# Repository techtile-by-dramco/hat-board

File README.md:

# HAT board ✅

This PCB was developed by Guus Leenders from KU Leuven DRAMCO and should be connected to the RPI 4 on all 140 tiles.
The board is utilized in a distributed antenna or **Radioweave** infrastructure and his main function is controlling the PLL board and OLED screen. 
This HAT board has a flat cable connector to control the PLL board (see [pll-oled-hat](https://github.com/techtile-by-dramco/pll-oled-hat))

All HAT board functions listed:
* 1x Flat cable connector (PLL board connection)
* 5x Addressable RGB LEDs
* 2x User buttons
* 1x HAT output connector
* 1x OLED screen
* 1x Proximity sensor

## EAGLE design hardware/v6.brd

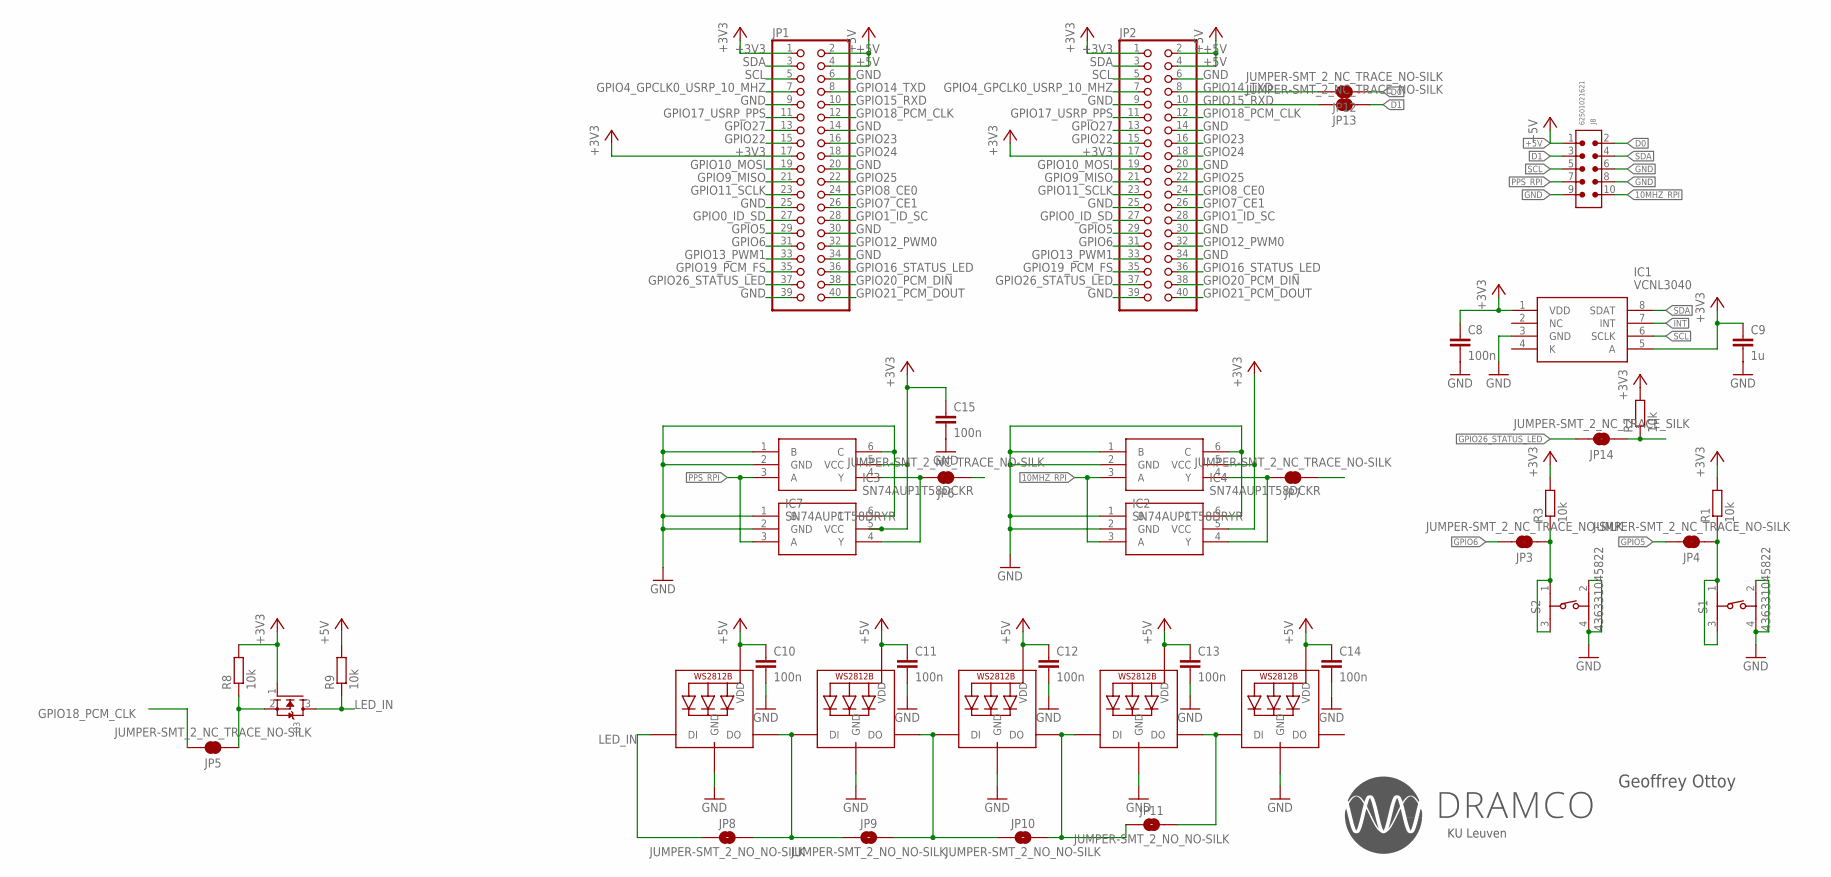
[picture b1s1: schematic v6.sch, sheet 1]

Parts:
C8, C10, C11, C12, C13, C14, C15: 100n; C0603
C9: 1u; C0603
IC1: VCNL3040; SON108P200X400X115-8N
IC2, IC7: SN74AUP1T58DRYR; SON50P100X145X60-6N
IC3, IC4: SN74AUP1T58DCKR; SOT65P210X110-6N
J8: 62501021621
JP1: PINHD-2X20; 2X20
JP2: PINHD-2X20/90; 2X20/90
JP3, JP4, JP5, JP6, JP7, JP12, JP13: JUMPER-SMT_2_NC_TRACE_NO-SILK; SMT-JUMPER_2_NC_TRACE_NO-SILK
JP8, JP9, JP10, JP11: JUMPER-SMT_2_NO_NO-SILK; SMT-JUMPER_2_NO_NO-SILK
JP14: JUMPER-SMT_2_NC_TRACE_SILK; SMT-JUMPER_2_NC_TRACE_SILK
LED1, LED2, LED3, LED4, LED5: WS2812B5050; WS2812B
Q3: MOSFET-NREFLOW; SOT23
R1, R2, R3, R8, R9: 10k; R0603
S1, S2: 436331045822; 4363X10458XX

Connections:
10MHZ_RPI: IC2.3 (A), IC4.3 (A), J8.10
+3V3: C8.1, C9.1, C15.1, IC1.1 (VDD), IC1.5 (A), IC2.5 (VCC), IC3.5 (VCC), IC4.5 (VCC), IC7.5 (VCC), JP1.1, JP1.17, JP2.1, JP2.17, Q3.1 (G), R1.2, R2.2, R3.2, R8.2; also elsewhere on the board
+5V: C10.1, C11.1, C12.1, C13.1, C14.1, J8.1, JP1.2, JP1.4, JP2.2, JP2.4, LED1.1-VDD (VDD), LED2.1-VDD (VDD), LED3.1-VDD (VDD), LED4.1-VDD (VDD), LED5.1-VDD (VDD), R9.2
D0: J8.2, JP12.1
D1: J8.3, JP13.1
GND: C8.2, C9.2, C10.2, C11.2, C12.2, C13.2, C14.2, C15.2, IC1.3 (GND), IC2.1 (B), IC2.2 (GND), IC2.6 (C), IC3.1 (B), IC3.2 (GND), IC3.6 (C), IC4.1 (B), IC4.2 (GND), IC4.6 (C), IC7.1 (B), IC7.2 (GND), IC7.6 (C), J8.6, J8.8, J8.9, JP1.6, JP1.9, JP1.14, JP1.20, JP1.25, JP1.30, JP1.34, JP1.39, JP2.6, JP2.9, JP2.14, JP2.20, JP2.25, JP2.30, JP2.34, JP2.39, LED1.3-GND (GND), LED2.3-GND (GND), LED3.3-GND (GND), LED4.3-GND (GND), LED5.3-GND (GND), S1.2 (4), S1.4 (2), S2.2 (4), S2.4 (2); also elsewhere on the board
GPIO0_ID_SD: JP1.27, JP2.27
GPIO1_ID_SC: JP1.28, JP2.28
GPIO4_GPCLK0_USRP_10_MHZ: JP1.7, JP2.7, JP7.1
GPIO5: JP1.29, JP2.29, JP4.2
GPIO6: JP1.31, JP2.31, JP3.2
GPIO7_CE1: JP1.26, JP2.26
GPIO8_CE0: JP1.24, JP2.24
GPIO9_MISO: JP1.21, JP2.21
GPIO10_MOSI: JP1.19, JP2.19
GPIO11_SCLK: JP1.23, JP2.23
GPIO12_PWM0: JP1.32, JP2.32
GPIO13_PWM1: JP1.33, JP2.33
GPIO14_TXD: JP1.8, JP2.8, JP12.2
GPIO15_RXD: JP1.10, JP2.10, JP13.2
GPIO16_STATUS_LED: JP1.36, JP2.36
GPIO17_USRP_PPS: JP1.11, JP2.11, JP6.1
GPIO18_PCM_CLK: JP1.12, JP2.12, JP5.2
GPIO19_PCM_FS: JP1.35, JP2.35
GPIO20_PCM_DIN: JP1.38, JP2.38
GPIO21_PCM_DOUT: JP1.40, JP2.40
GPIO22: JP1.15, JP2.15
GPIO23: JP1.16, JP2.16
GPIO24: JP1.18, JP2.18
GPIO25: JP1.22, JP2.22
GPIO26_STATUS_LED: JP1.37, JP2.37, JP14.2
GPIO27: JP1.13, JP2.13
INT: IC1.7 (INT), JP14.1, R2.1
LED_IN: JP8.1, LED1.4-DIN (DI), Q3.3 (D), R9.1
unnamed: IC3.4 (Y), IC7.4 (Y), JP6.2
unnamed: JP5.1, Q3.2 (S), R8.1
unnamed: IC2.4 (Y), IC4.4 (Y), JP7.2
unnamed: JP3.1, R3.1, S2.1 (3), S2.3 (1)
unnamed: JP8.2, JP9.1, LED1.2-DOUT (DO), LED2.4-DIN (DI)
unnamed: JP9.2, JP10.1, LED2.2-DOUT (DO), LED3.4-DIN (DI)
unnamed: JP10.2, JP11.1, LED3.2-DOUT (DO), LED4.4-DIN (DI)
unnamed: JP11.2, LED4.2-DOUT (DO), LED5.4-DIN (DI)
unnamed: JP4.1, R1.1, S1.1 (3), S1.3 (1)
PPS_RPI: IC3.3 (A), IC7.3 (A), J8.7
SCL: IC1.6 (SCLK), J8.5, JP1.5, JP2.5; also elsewhere on the board
SDA: IC1.8 (SDAT), J8.4, JP1.3, JP2.3; also elsewhere on the board

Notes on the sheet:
Geoffrey Ottoy
KU Leuven

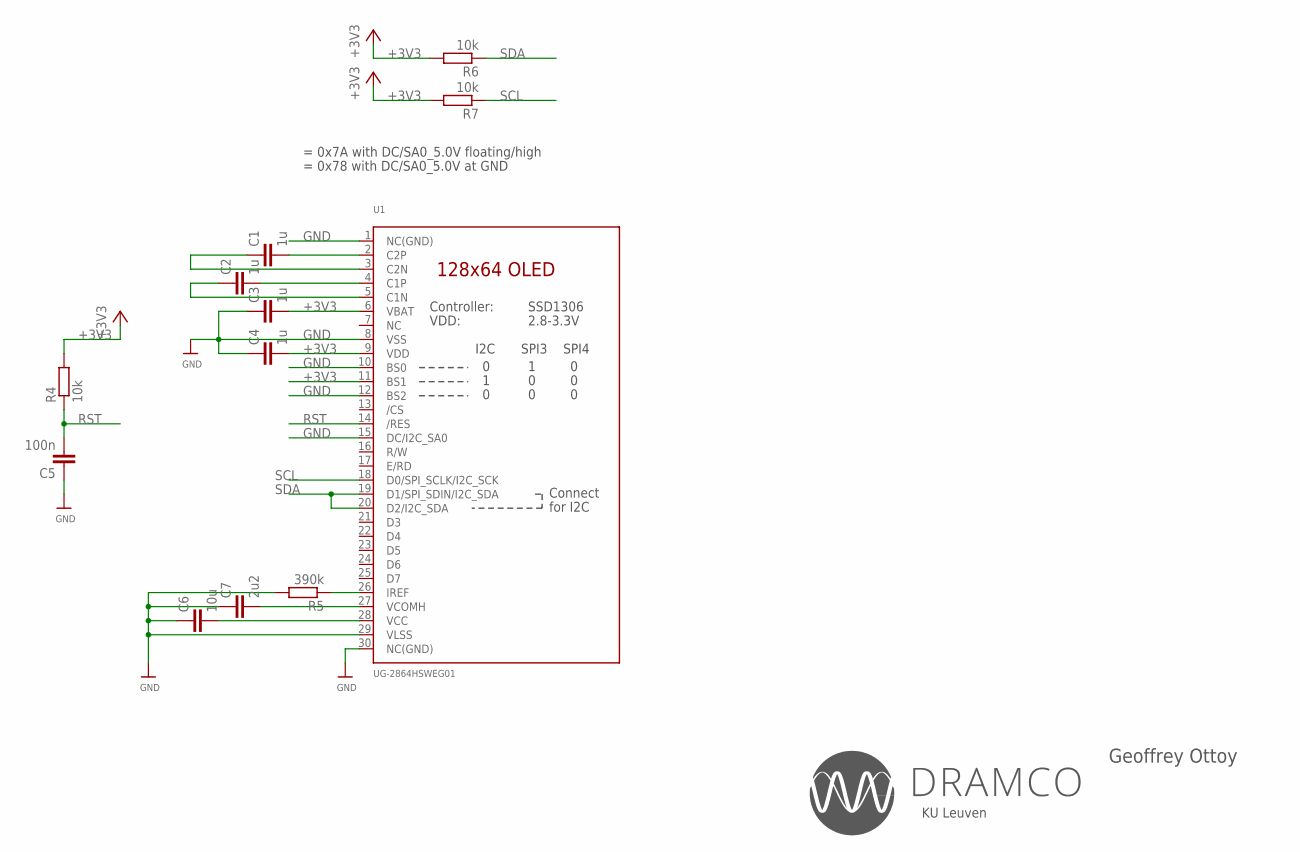
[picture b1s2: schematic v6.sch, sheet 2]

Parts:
C1, C2, C3, C4: 1u; C0603
C5: 100n; C0603
C6: 10u; C0603
C7: 2u2; C0603
R4, R6, R7: 10k; R0603
R5: 390k; R0603
U1: UG-2864HSWEG01; UG-2864HSWEG01_0.96IN_WRAPAROUND

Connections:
+3V3: C3.2, C4.2, R4.2, R6.2, R7.2, U1.6 (VBAT), U1.9 (VDD), U1.11 (BS1); also elsewhere on the board
GND: C3.1, C4.1, C5.1, C6.1, C7.1, R5.2, U1.1 (NC(GND)), U1.8 (VSS), U1.10 (BS0), U1.12 (BS2), U1.15 (DC/I2C_SA0), U1.29 (VLSS), U1.30 (NC(GND)); also elsewhere on the board
unnamed: C1.2, U1.2 (C2P)
unnamed: C6.2, U1.28 (VCC)
unnamed: C7.2, U1.27 (VCOMH)
unnamed: R5.1, U1.26 (IREF)
unnamed: C1.1, U1.3 (C2N)
unnamed: C2.2, U1.4 (C1P)
unnamed: C2.1, U1.5 (C1N)
RST: C5.2, R4.1, U1.14 (/RES)
SCL: R7.1, U1.18 (D0/SPI_SCLK/I2C_SCK); also elsewhere on the board
SDA: R6.1, U1.19 (D1/SPI_SDIN/I2C_SDA), U1.20 (D2/I2C_SDA); also elsewhere on the board

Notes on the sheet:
= 0x7A with DC/SA0_5.0V floating/high
= 0x78 with DC/SA0_5.0V at GND
Geoffrey Ottoy
KU Leuven

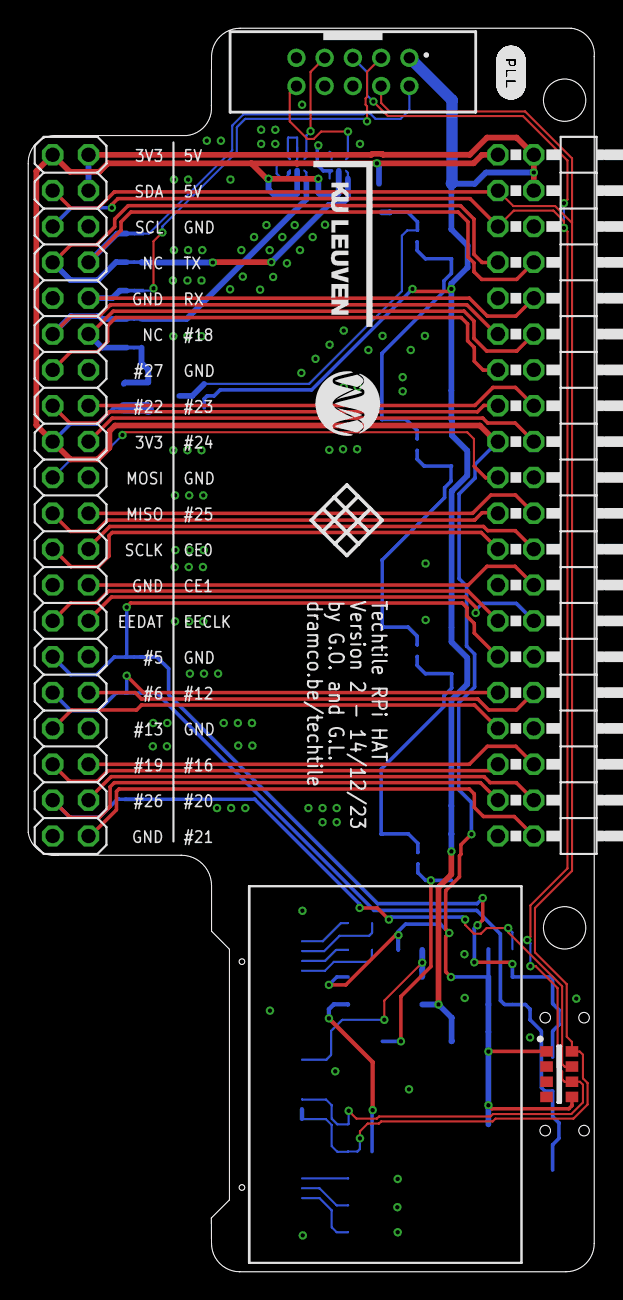
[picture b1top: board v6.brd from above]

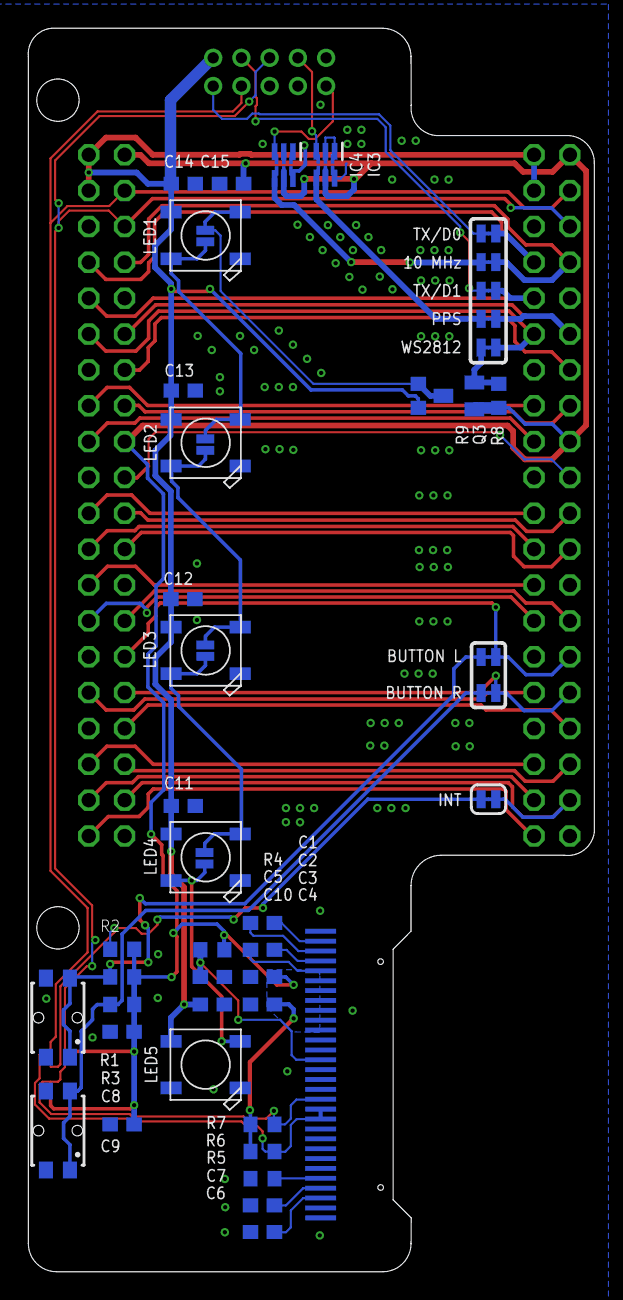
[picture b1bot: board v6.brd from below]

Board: 2 copper layers, 40.1 x 88.1 mm, 53 parts (48 on the bottom side), 54 nets.

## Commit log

2024-02-27 Change of structure
2024-04-05 Changed connector

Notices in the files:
parts and their libraries:
microbuilder: This work is placed in the public domain, and may be freely used for commercial and non-commercial work with the following conditions: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
Eagle_WR-BHD: Copyright: Würth Elektronik
